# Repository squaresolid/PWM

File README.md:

PWM
===

PWM circuits collection

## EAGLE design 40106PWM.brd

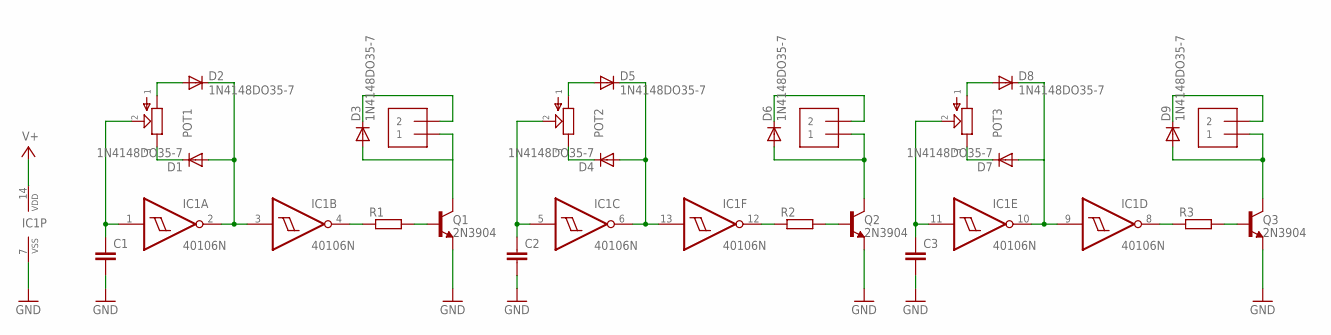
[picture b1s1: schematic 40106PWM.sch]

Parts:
C1, C2, C3: C-EU050-025X075; C050-025X075
D1, D2, D3, D4, D5, D6, D7, D8, D9: 1N4148DO35-7; DO35-7
IC1: 40106N; DIL14
J1, J2, J3: 1X2-3.5MM
POT1, POT2, POT3: POT-EU16MM; 16MM
Q1, Q2, Q3: 2N3904; TO92-
R1, R2, R3: R-EU_0207/10; 0207/10

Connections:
GND: C1.2, C2.2, C3.2, IC1.7 (VSS), Q1.3 (E), Q2.3 (E), Q3.3 (E)
unnamed: D1.A, D2.C, IC1.2 (O), IC1.3 (I)
unnamed: D4.A, D5.C, IC1.6 (O), IC1.13 (I)
unnamed: D7.A, D8.C, IC1.9 (I), IC1.10 (O)
unnamed: D2.A, POT1.1
unnamed: C3.1, IC1.11 (I), POT3.2
unnamed: C1.1, IC1.1 (I), POT1.2
unnamed: C2.1, IC1.5 (I), POT2.2
unnamed: D1.C, POT1.3
unnamed: IC1.4 (O), R1.1
unnamed: Q1.2 (B), R1.2
unnamed: D3.A, J1.1, Q1.1 (C)
unnamed: D3.C, J1.2
unnamed: D5.A, POT2.1
unnamed: D4.C, POT2.3
unnamed: IC1.12 (O), R2.1
unnamed: Q2.2 (B), R2.2
unnamed: D6.A, J2.1, Q2.1 (C)
unnamed: D6.C, J2.2
unnamed: D8.A, POT3.1
unnamed: D7.C, POT3.3
unnamed: IC1.8 (O), R3.1
unnamed: Q3.2 (B), R3.2
unnamed: D9.A, J3.1, Q3.1 (C)
unnamed: D9.C, J3.2
V+: IC1.14 (VDD)

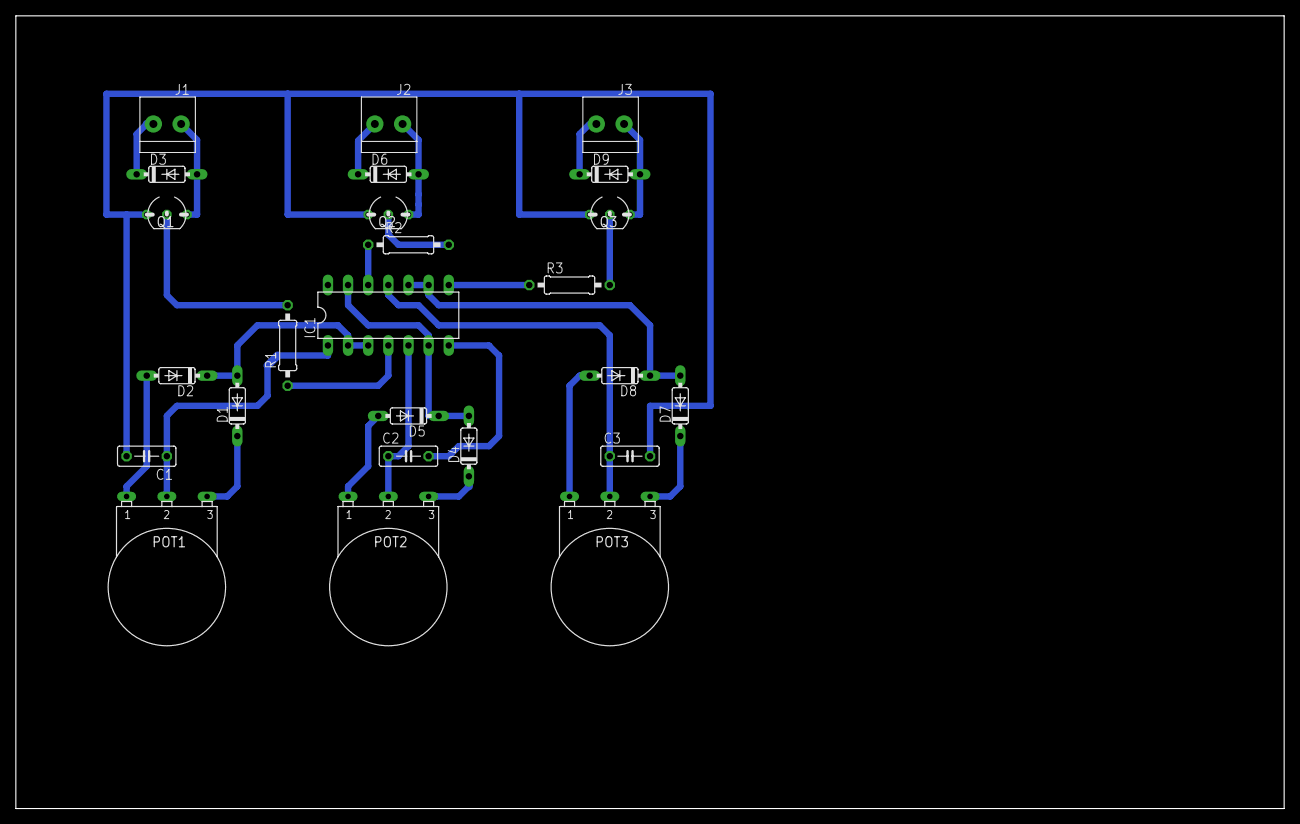
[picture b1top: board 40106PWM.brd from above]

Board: 2 copper layers, 160.0 x 100.0 mm, 25 parts (0 on the bottom side), 25 nets.

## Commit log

2014-08-19 40106PWM.sch
2014-08-19 40106PWM.brd
